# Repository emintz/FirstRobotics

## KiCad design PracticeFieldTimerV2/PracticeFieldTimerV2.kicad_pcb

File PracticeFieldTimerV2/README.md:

# Metuchen Momentum Countdown Timer

## License

The countdown timer hardware design is made available subject to the terms of the
CERN Open Hardware Licence Version 2 - Strongly Reciprocal. A copy should have been
provided to you. If you have not been provided with a copy, you can download one from
https://cern-ohl.web.cern.ch/ pdf
[pdf](https://gitlab.com/ohwr/project/cernohl/-/wikis/uploads/b236492596cfc91c12def7d50bbf7da0/cern_ohl_s_v2.pdf)
or
[plain text](https://gitlab.com/ohwr/project/cernohl/-/wikis/uploads/819d71bea3458f71fba6cf4fb0f2de6b/cern_ohl_s_v2.txt)
format.

## Background

The printed circuit board is a follow-on project to the prototype
countdown timer used to manage the practice field during the 2026
FIRST Mid-Atlantic championship competition. Everyone involved
considered it successful. The prototypes were immature, far too
fragile to withstand routine handling during transportation and
storage. It is hoped that the printed circuit board-based design
will meet this need.

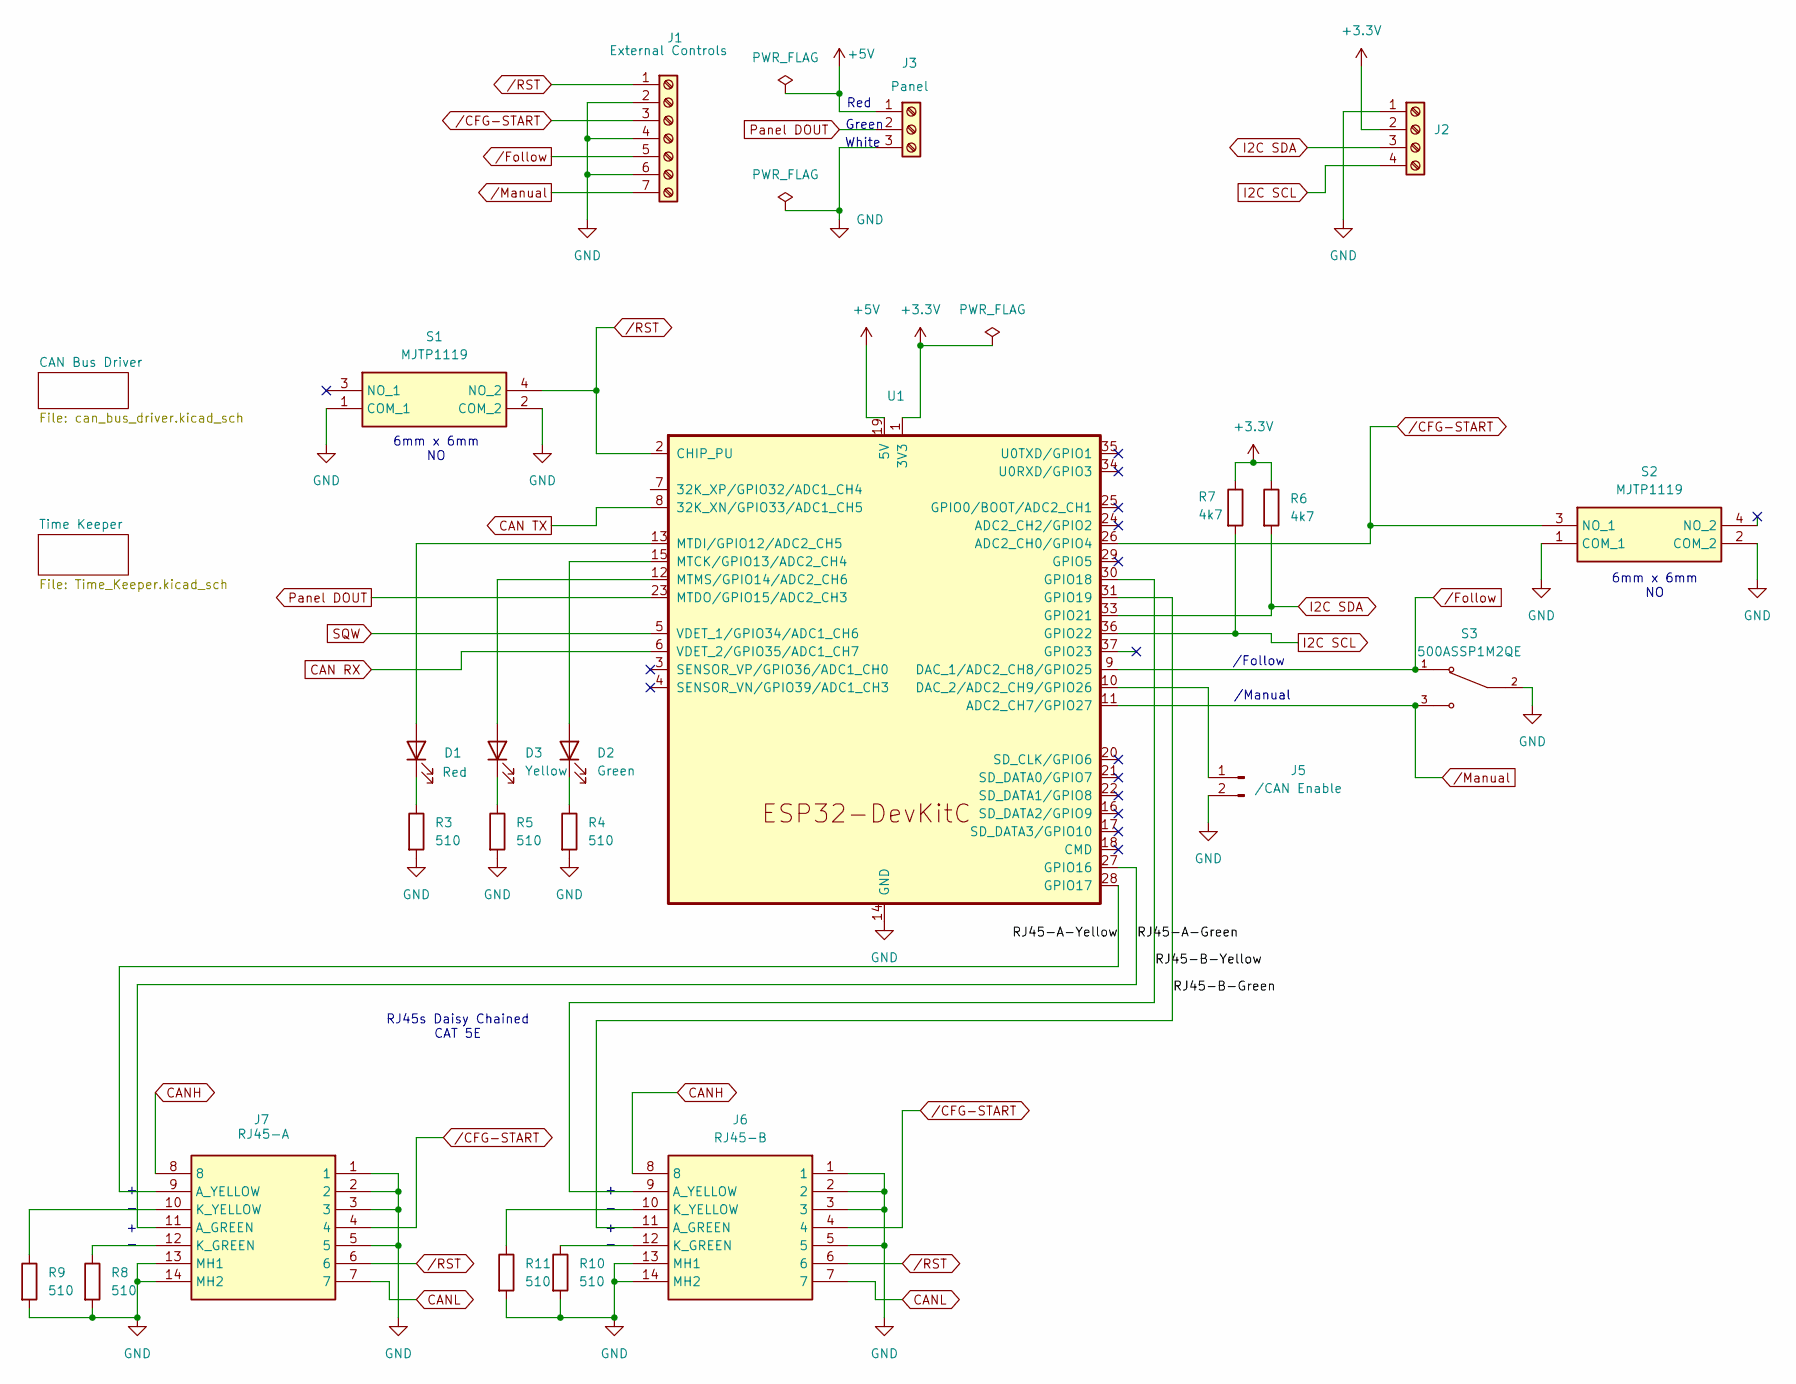
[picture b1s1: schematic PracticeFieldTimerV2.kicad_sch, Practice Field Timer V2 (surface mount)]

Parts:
D1: Red; LED_D5.0mm-PCBWay-Compatible
D2: Green; LED_D5.0mm-PCBWay-Compatible
D3: Yellow; LED_D5.0mm-PCBWay-Compatible
J1: External Controls; TerminalBlock_MaiXu_MX126-5.0-07P_1x07_P5.00mm
J2: Screw_Terminal_01x04; TerminalBlock_MaiXu_MX126-5.0-04P_1x04_P5.00mm
J3: Panel; TerminalBlock_MaiXu_MX126-5.0-03P_1x03_P5.00mm
J5: /CAN Enable; PinHeader_1x02_P2.54mm_Vertical
J6: RJ45-B; MTJ88TX1FSDLG; Manufacturer_Part_Number MTJ-88TX1-FSD-LG; Mouser Part Number 737-MTJ-88TX1-FSD-LG
J7: RJ45-A; MTJ88TX1FSDLG; Manufacturer_Part_Number MTJ-88TX1-FSD-LG; Mouser Part Number 737-MTJ-88TX1-FSD-LG
R3, R4, R5, R8, R9, R10, R11: 510; R_Axial_DIN0207_L6.3mm_D2.5mm_P15.24mm_Horizontal
R6, R7: 4k7; R_Axial_DIN0207_L6.3mm_D2.5mm_P15.24mm_Horizontal
S1, S2: MJTP1119; Manufacturer_Part_Number MJTP1119; Mouser Part Number 642-MJTP1119
S3: 500ASSP1M2QE; SW_500ASSP1M2QE; PARTREV G
U1: ESP32-DevKitC

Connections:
+3.3V: J2.2, R6.1, R7.1, U1.1 (3V3); also elsewhere on the board
+5V: J3.1, U1.19 (5V)
/RJ45-A-Green: J7.11 (A_GREEN), U1.27 (GPIO16)
/RJ45-A-Yellow: J7.9 (A_YELLOW), U1.28 (GPIO17)
/RJ45-B-Green: J6.11 (A_GREEN), U1.31 (GPIO19)
/RJ45-B-Yellow: J6.9 (A_YELLOW), U1.30 (GPIO18)
CAN RX: U1.6 (VDET_2/GPIO35/ADC1_CH7); also elsewhere on the board
CAN TX: U1.8 (32K_XN/GPIO33/ADC1_CH5); also elsewhere on the board
CANH: J6.8, J7.8; also elsewhere on the board
CANL: J6.7, J7.7; also elsewhere on the board
GND: J1.2, J1.4, J1.6, J2.1, J3.3, J5.2, J6.1, J6.2, J6.3, J6.5, J6.13 (MH1), J6.14 (MH2), J7.1, J7.2, J7.3, J7.5, J7.13 (MH1), J7.14 (MH2), R3.2, R4.2, R5.2, R8.2, R9.2, R10.2, R11.2, S1.1 (COM_1), S1.2 (COM_2), S2.1 (COM_1), S2.2 (COM_2), S3.2, U1.14 (GND), U1.32 (GND), U1.38 (GND); also elsewhere on the board
I2C SCL: J2.4, R7.2, U1.36 (GPIO22); also elsewhere on the board
I2C SDA: J2.3, R6.2, U1.33 (GPIO21); also elsewhere on the board
unnamed: D1.2 (A), U1.13 (MTDI/GPIO12/ADC2_CH5)
unnamed: D1.1 (K), R3.1
unnamed: D2.2 (A), U1.15 (MTCK/GPIO13/ADC2_CH4)
unnamed: D2.1 (K), R4.1
unnamed: D3.2 (A), U1.12 (MTMS/GPIO14/ADC2_CH6)
unnamed: D3.1 (K), R5.1
unnamed: J5.1, U1.10 (DAC_2/ADC2_CH9/GPIO26)
unnamed: J6.12 (K_GREEN), R10.1
unnamed: J6.10 (K_YELLOW), R11.1
unnamed: J7.12 (K_GREEN), R8.1
unnamed: J7.10 (K_YELLOW), R9.1
Panel DOUT: J3.2, U1.23 (MTDO/GPIO15/ADC2_CH3)
SQW: U1.5 (VDET_1/GPIO34/ADC1_CH6); also elsewhere on the board
/CFG-START: J1.3, J6.4, J7.4, S2.3 (NO_1), U1.26 (ADC2_CH0/GPIO4)
/Follow: J1.5, S3.1, U1.9 (DAC_1/ADC2_CH8/GPIO25)
/Manual: J1.7, S3.3, U1.11 (ADC2_CH7/GPIO27)
/RST: J1.1, J6.6, J7.6, S1.4 (NO_2), U1.2 (CHIP_PU)

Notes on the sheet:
Red
6mm x 6mm NO
Green
White
/Manual
/Follow
RJ45s Daisy Chained CAT 5E

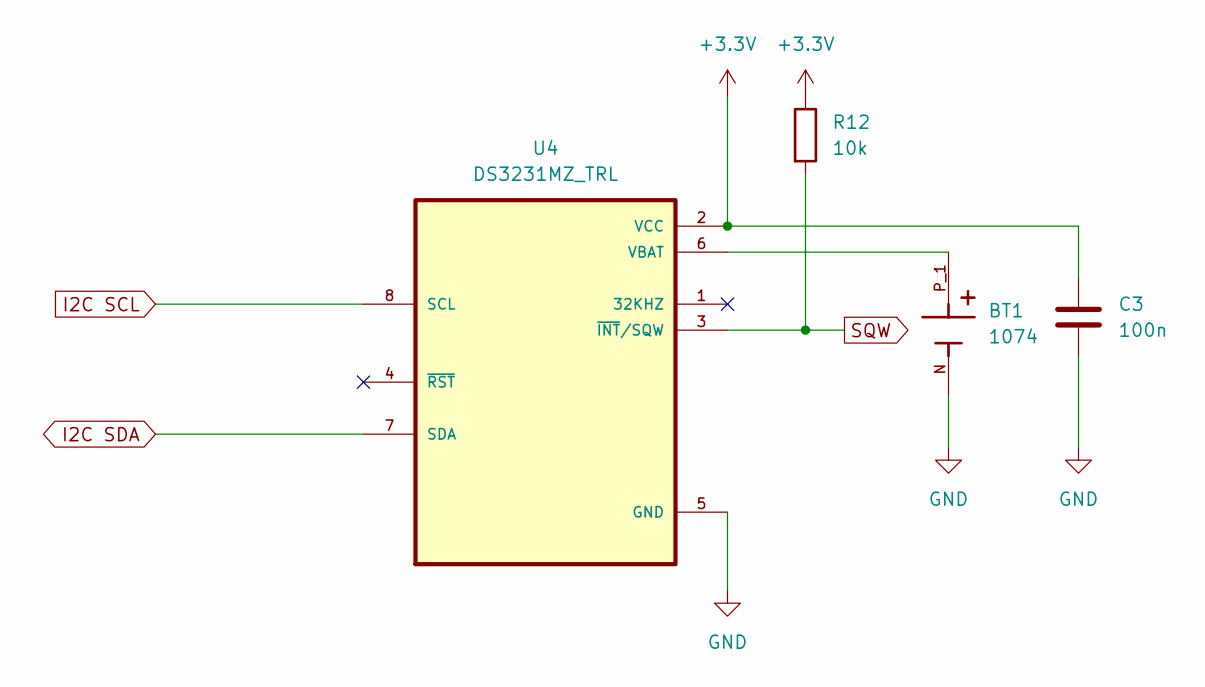
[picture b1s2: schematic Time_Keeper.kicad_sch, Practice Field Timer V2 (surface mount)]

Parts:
BT1: 1074; BAT_1074; PARTREV B
C3: 100n; C_Disc_D5.0mm_W2.5mm_P5.00mm
R12: 10k; R_Axial_DIN0207_L6.3mm_D2.5mm_P15.24mm_Horizontal
U4: DS3231MZ_TRL; 21-0041B_8_MXM

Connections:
+3.3V: C3.1, R12.1, U4.2 (VCC); also elsewhere on the board
GND: BT1.N, C3.2, U4.5 (GND); also elsewhere on the board
I2C SCL: U4.8 (SCL); also elsewhere on the board
I2C SDA: U4.7 (SDA); also elsewhere on the board
unnamed: BT1.P_1, BT1.P_2, U4.6 (VBAT)
SQW: R12.2, U4.3 (~INT/SQW); also elsewhere on the board

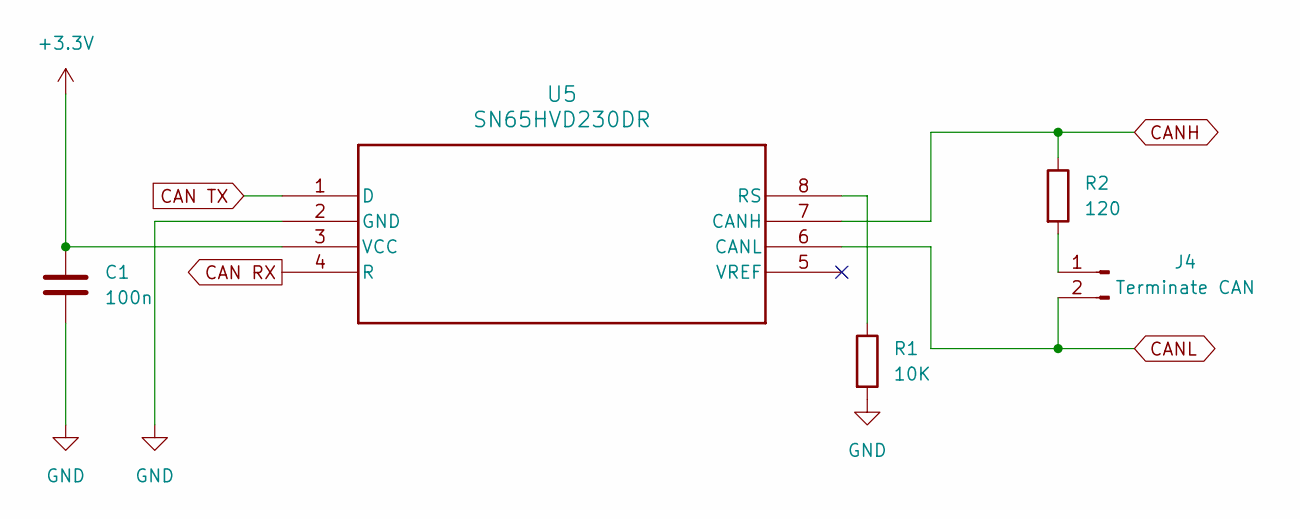
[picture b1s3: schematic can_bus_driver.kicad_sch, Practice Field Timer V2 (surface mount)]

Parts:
C1: 100n; C_Disc_D5.0mm_W2.5mm_P5.00mm
J4: Terminate CAN; PinHeader_1x02_P2.54mm_Vertical
R1: 10K; R_Axial_DIN0207_L6.3mm_D2.5mm_P15.24mm_Horizontal
R2: 120; R_Axial_DIN0207_L6.3mm_D2.5mm_P15.24mm_Horizontal
U5: SN65HVD230DR

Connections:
+3.3V: C1.1, U5.3 (VCC); also elsewhere on the board
CAN RX: U5.4 (R); also elsewhere on the board
CAN TX: U5.1 (D); also elsewhere on the board
CANH: R2.1, U5.7 (CANH); also elsewhere on the board
CANL: J4.2, U5.6 (CANL); also elsewhere on the board
GND: C1.2, R1.2, U5.2 (GND); also elsewhere on the board
unnamed: J4.1, R2.2
unnamed: R1.1, U5.8 (RS)

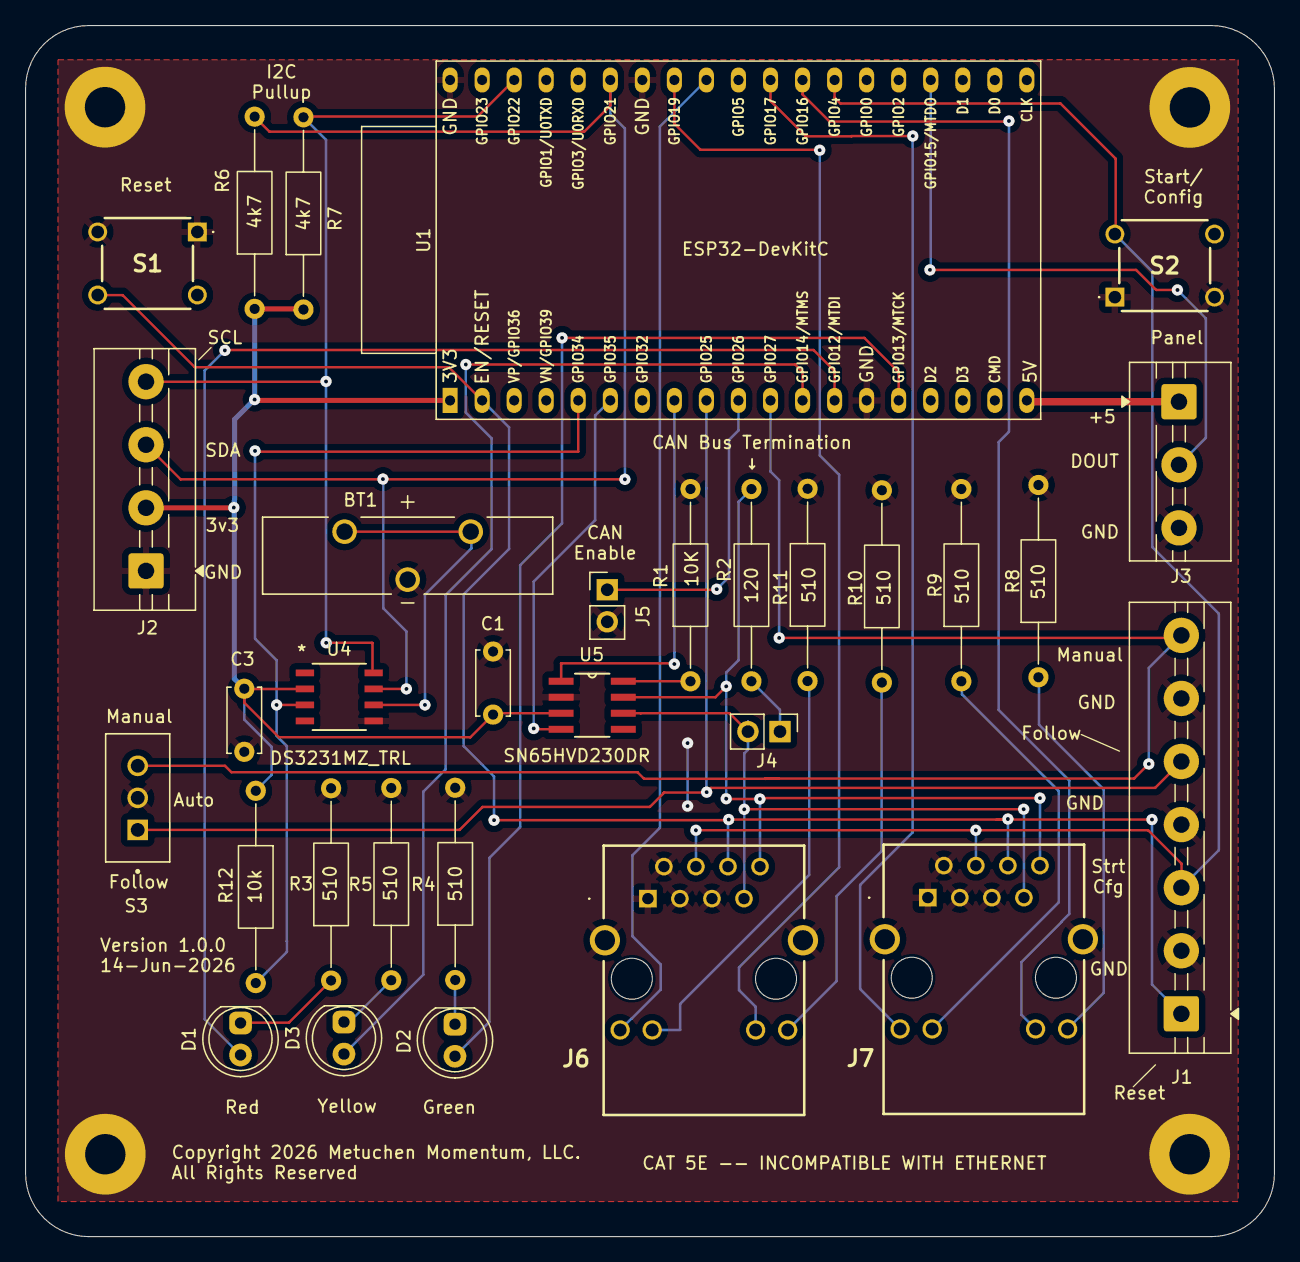
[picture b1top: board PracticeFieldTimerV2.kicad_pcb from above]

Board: 2 copper layers, 99.0 x 96.0 mm, 37 parts (1 on the bottom side), 33 nets.

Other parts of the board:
Logo80%: LOGO; MetuchenMomentumLogo80Percent
MH1, MH2, MH3, MH4: MountingHole_3.2mm_M3_Pad_TopBottom_Grounded
MH3#2: (no value)

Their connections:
GND: MH1.1, MH2.2, MH3.3, MH3#2.3, MH4.4; also elsewhere on the board

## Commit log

2025-05-23 Baseline implementation. Supports configuration and free-running countdown. Does not yet synchronize the continuous count down with practice field opening time.
2025-05-23 Flesh out .gitignore.
2025-05-24 Synchronize continuous count down to the reference time. Remove unused background color from the display command. Document.
2025-06-08 Fix Typoz in headers.
2025-06-09 Second major code tranche: start to integrate the CAN bus.
2025-06-11 Prepare to integrate the CAN bus by decoupling the red LED from the time display and adding the required configuration pins, a CAN Enable pin to simplify debugging, and a Leader/Follower selection pi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
    Basically, both the leader and follower will nominally respect
    time display commands received on the CAN bus. However, only
    the one leader will send them and, since CAN bus nodes normally
    do not receive the messages they send, only the followers
    will receive them. The messages are sent from the time
    source, which only the leader will run.
2025-06-12 Nightly commit: Enable follower mode when FOLLOWER_NOT_PIN is LOW. Enable CAN bus when CAN_ENABLE_NOT_PIN pin is LOW. Disable time source in follower. Leader publishes time changes to CAN bus, if ena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
    Code is in rough shape and needs massive cleanup, but we now
    have a solid proof of concept.
2025-06-13 Clean up: delete unused/commented out code, delete or commment out obsolete debug prints.
2025-06-13 Document operator() and display transmit status using the red and green LEDs.
2025-06-13 Position the countdown classes to support one shot operation.
2025-06-13 Partial implementation of the one shot countdown (nightly commit)
2025-06-17 Manual countdown initial version. Needs cleanup. Daily submit for safety.
2025-06-18 Separate Leader/Follower pin from the Continuous/One Shot pin. Clear the display when manual countdown is not running. Fix bugs.
    The code needs cleanup. This is a backup by means of a commit/push.
2025-06-19 Commend, clean up, and add license. No substantive changes to logic.
2025-06-19 Refactor convenience display command publication. Implement it in the one shot countdown and replace the manual countdown implementation with an inline forwarder. Also change the API name to be more 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
2025-06-19 Restore startup delay so as to display the test pattern on power up. Start the CAN bus (if enabled) before displaying the test pattern. This completes the prototype timer.
2025-06-20 Spiff the script up a bit more. Comment all methods, add a bit more progress logging.
2025-06-22 Fix minor format violation and add a bit of logging.
2025-06-22 Rationalize GPIO setup, consolidate it in setup().
2025-07-02 Start integrating the LCD status display -- daily commit
2025-07-08 Display WiFi settings, including the network password, on the LCD during setup. Note that security doesn't matter all that much, but it is useful to require that the configuration be set by someone w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
2025-07-24 Remove unused color tracking pin definitions, as we are using an LCD to display status.
2025-08-08 Add license.
2025-08-08 Minor format fix: delete unnecessary and unwanted whitespace.
2025-08-08 Double timer stack size to reduce overflow risk.
2025-08-08 Chain panel update with flooding. Minor format fix for clarity.
2025-08-08 Fix suspected race condition. Split "Leader" status into "Manual" and "Auto" depending on mode.
2025-08-08 Disable debug output.
2025-08-08 Remove one confusing line of debug print. Pause after displaying "Follow" in follower mode to avoid race condition or possibly to appease the Bug Demons.
2025-12-04 Minor cleanup after failed attempt to calibrate the DS3231 from the configuration web page.
2025-12-16 Support setting the time source date/time.
2025-12-16 Pass the web server to the Configurator per the latest Property Page Library changes.
2025-12-21 Add DS3231 calibration to the configuration settings.
2025-12-21 Cosmetic fixes to web pages.
2025-12-21 Display startup status on the panel, plus one cosmetic change.
2025-12-21 Shorten the startup wait.
2025-12-22 Replace flood panel with black with panel clear.
2025-12-22 Display 'WAIT' between property update and timer start. Remove unnecessary wait. Rearrange subsystem initialization to eliminate panel display artifacts.
2025-12-22 Fix "SETUP" bitmap.
2025-12-22 Hide the Unix time field in the time calibration landing page.
2025-12-23 Remove obsolete test pattern. We have replaced it with meaningful status messages.
2025-12-23 Add ESP32 breakout board pinout.
2025-12-31 Fix WiFi setup.
2026-01-01 Add copyright, licence, and documentation.
2026-01-01 Add more documentation. Blink the builtin LED at 1 Hz on success. Blink it faster on failure.
2026-01-03 Ignore the Sloeber-specific .project file.
2026-01-06 Provide a stand-alone software update script. Switch from the Adafruit Real Time Clock library to the simpler version by NeiroN (neiron.nxn@gmail.com). Ignore *.bak
2026-05-08 Document the KiCad symbol for the ESP32 module uses herein.
2026-05-10 Practice Field Timer initial commit
2026-05-10 Clean up and assign most footprints. Need footprint for decoupling capacitor.
2026-05-11 Finish filling in footprints.
2026-05-17 Resolved most errors. Still need to add mounting holes and define the board boundary. Also, the I2C header is way too close to the LCD and need to move. The required changes are unclear.
2026-05-17 Fix LCD header, which was wired backwards.
2026-05-18 Adjust part placement and routing. Annotate the board with copyright &c. Set the edges. Next step: mounting holes.
2026-05-18 Add mounting holes. Note that the LCD Module mounting holes will do double duty. Label more parts and clean up a bit more.
2026-05-20 Move traces away from the RJ-45 jacks, which appear to have metal jackets. Add detail to annotations, correct typoz, adjust fonts.
2026-05-20 Set schematic size to US Letter and adjust placements to fit. Add copyright notice and team logo.
2026-05-21 Improve comments.
2026-05-21 Round the PCB corners, set the fill copper back from the edge, Align text, change to clear LEDs on 3-D view to avoid confusion.
2026-05-21 Uncross CAN Transmit and CAN Receive. They were interchanged.
2026-05-22 Print schematic on US Letter paper. Do not commit output files like Gerber and PDF.
2026-05-27 Exclude vestigial directory
2026-05-27 Fix mounting hole properties, chamfer ground plane corners, fillet (round) board edges
2026-05-27 Document GPIO assignments.
2026-05-28 Rearrange labels to improve appearance and legibility.
2026-05-28 Fix push button connections.
2026-05-30 Add DS3231
2026-06-01 Morar blinkinlights: connect the LEDs on the RJ45 jacks to ESP32 pins. Can have too many blinkers!
2026-06-02 Mark resistors with values. Add mounting holes for the LCD display. Needlessy tweak board width.
2026-06-02 Fix traces broken in the previous commit.
2026-06-02 Clean up LCD mounting holes.
2026-06-02 More cleanup: redraw the cut lines to precise dimensions, minor improvements to symbol appearance.
2026-06-03 Fix egregious wiring error in the LCD Display
2026-06-03 Fix reversed power and ground on LCD backlight LED.
2026-06-04 Power the LCD backlight from +5 to minimize load on the ESP32 voltage reducer and for maximum brightness.
2026-06-09 Remove on-board LCD Module and I2C->parallel byte converter. Add terminal strip for off-board display. Shrink the board. The board is still a bit spread out, but the changes are significant enough to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
2026-06-09 Finish shrinking the board. Could do more, but the benefit doesn't justify the effort.
2026-06-09 Add missing resistors. Fix the warnings we can. Cosmetic fixes. Getting close
2026-06-10 Smush components closer together to reduce width under 100 mm because cost of manufacture. Tidied up a bit. Added missing labels. In short: mucked about.
2026-06-11 Enforce 8 Mil/.2032 mm track spacing to minimize manufacturing cost.
2026-06-11 Replace micro via with plain old via to minimize manufacturing cost and because the N00B designer doesn't understand the difference. So there!
2026-06-12 Add 10K pullup to SQW per DS3231 datasheet. Silly me!
2026-06-13 Adjust traces to neaten layout a bit. Add bridge to unfilled area. Add meaningful reference codes to the mounting holes to eliminate duplicate footprint warnings.
2026-06-13 Tidy the schematic. Ground both common pins on push buttons.
2026-06-13 Minor faffing about with reference numbers.
2026-06-14 Add version number and perform final cleanup prior to requesting fab quotes.
2026-06-14 As ordered: changed mounting holes pads to through hole, minor trace adjustments, checked everything, uplocated to PCBWay. Awaiting verification so I can complete the order.
2026-06-25 Change the CAN input GPIO pin from 32, which supports input and output and provides pullup and pulldown resistors, to pin 35, an input-only pin berift of resistors, thereby freeing a full-featured GP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
    NOTE THAT THIS IS A BREAKING CHANGE. The changed software WILL NOT RUN
    on the two prototypes used at Lehigh in the spring of 2026. It will
    run on the PCB platform.
2026-06-25 Dump ESP32 chip information: core count, model name, etc. during startup. Has no other effects.
2026-06-26 Deprecate and prepare to delete the initial schematic. It won't work.
2026-06-26 Set terms of use.
2026-06-26 Clean up README -- minor editorial changes.
2026-06-27 Add jumper pins to control CAN bus termination. Counters at the end of the CAN bus MUST connect the pins. Others MUST leave the pins disconnected.
2026-06-27 Blink the RJ-45 LEDs to indicate CAN bus activity. Green signals transmission; yellow signals receipt.

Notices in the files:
PracticeFieldTimer/PracticeFieldTimer-38-pin-ESP32s2/can_bus_driver.kicad_sch:
Copyright 2026, Metuchen Momentum LLC, All Rights Reserved
